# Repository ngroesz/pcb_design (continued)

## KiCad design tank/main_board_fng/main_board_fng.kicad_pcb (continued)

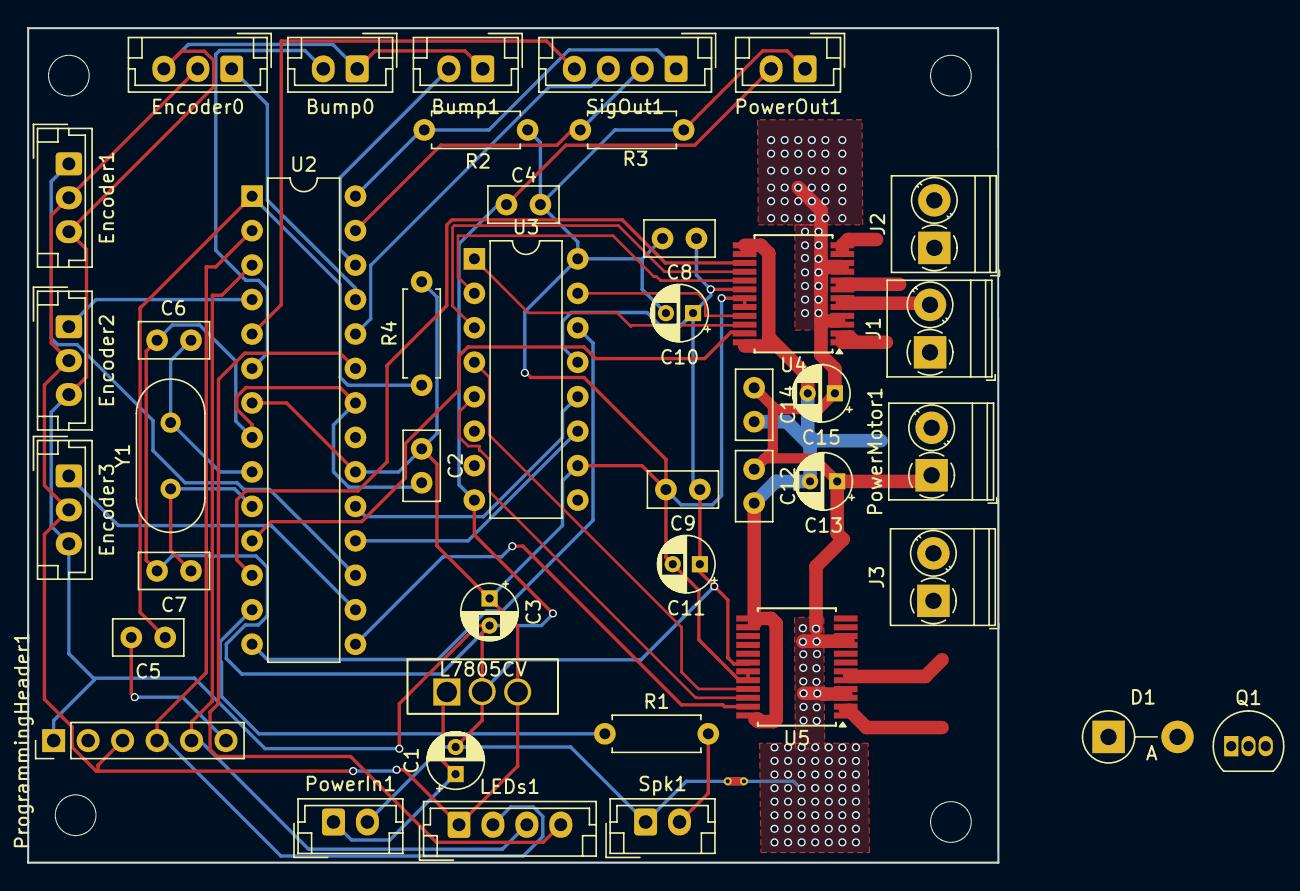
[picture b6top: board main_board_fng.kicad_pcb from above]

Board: 2 copper layers, 71.5 x 61.5 mm, 48 parts (0 on the bottom side), 44 nets.

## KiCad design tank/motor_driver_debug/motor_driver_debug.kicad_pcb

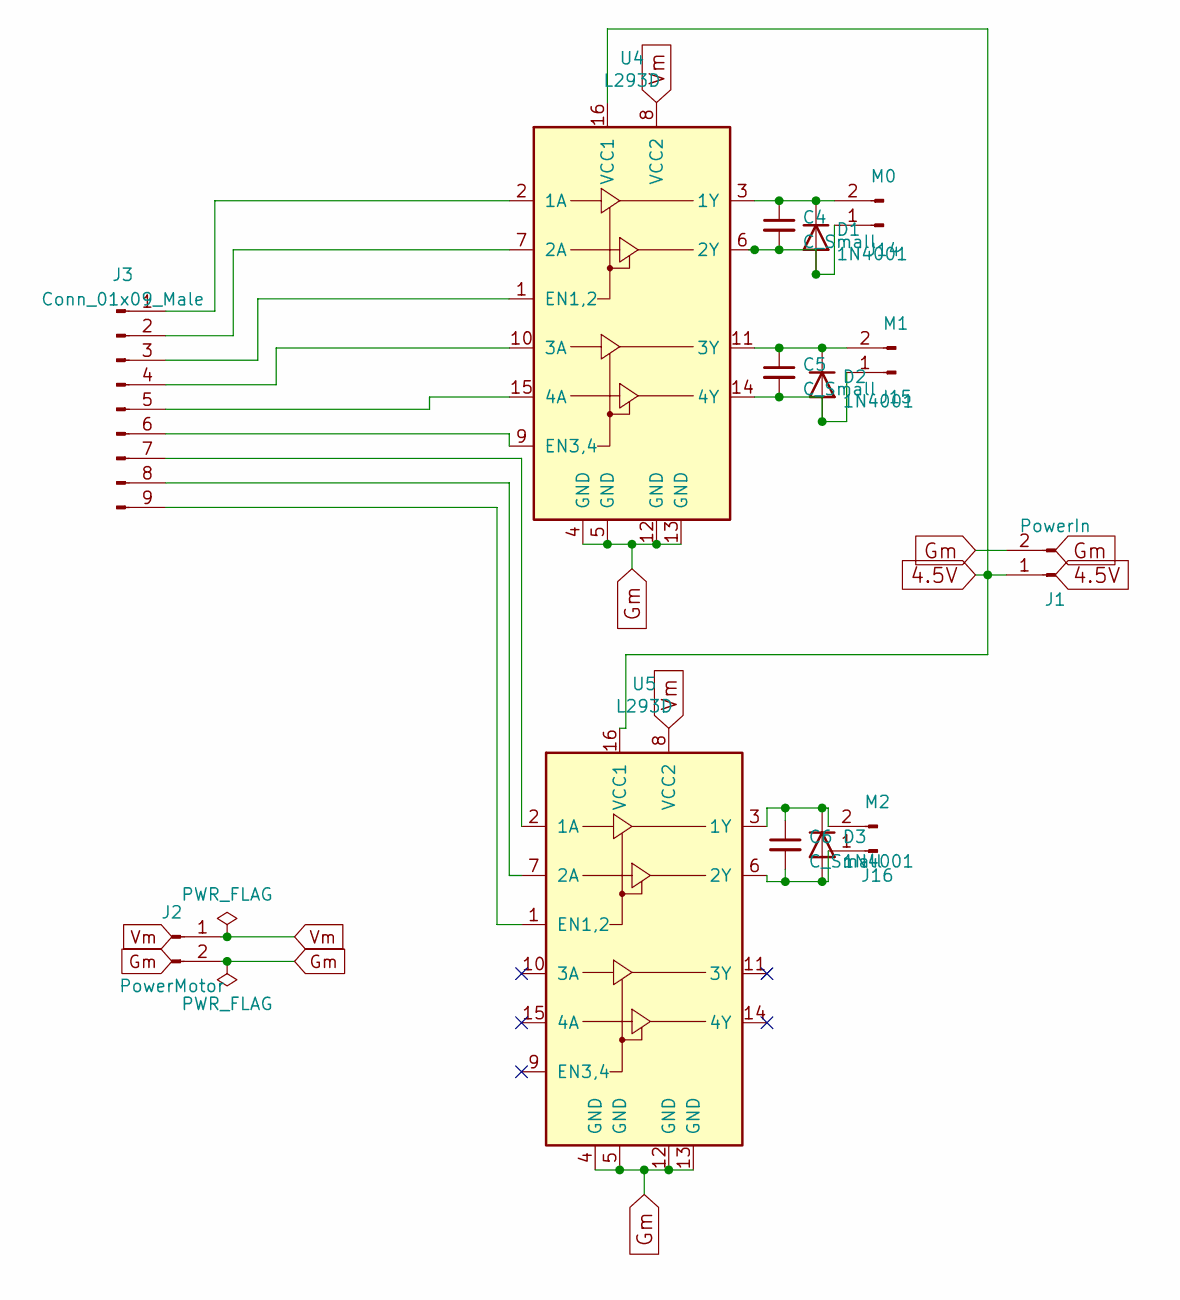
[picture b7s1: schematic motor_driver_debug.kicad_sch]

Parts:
C4, C5, C6: C_Small; C_Disc_D4.7mm_W2.5mm_P5.00mm
D1, D2, D3: 1N4001; D_DO-41_SOD81_P10.16mm_Horizontal
J1: PowerIn; JST_EH_B2B-EH-A_1x02_P2.50mm_Vertical
J2: PowerMotor; JST_EH_B2B-EH-A_1x02_P2.50mm_Vertical
J3: Conn_01x09_Male; JST_EH_B9B-EH-A_1x09_P2.50mm_Vertical
J14: M0; JST_EH_B2B-EH-A_1x02_P2.50mm_Vertical
J15: M1; JST_EH_B2B-EH-A_1x02_P2.50mm_Vertical
J16: M2; JST_EH_B2B-EH-A_1x02_P2.50mm_Vertical
U4, U5: L293D; DIP-16_W7.62mm

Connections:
4.5V: J1.1, U4.16 (VCC1), U5.16 (VCC1)
Gm: J1.2, J2.2, U4.4 (GND), U4.5 (GND), U4.12 (GND), U4.13 (GND), U5.4 (GND), U5.5 (GND), U5.12 (GND), U5.13 (GND)
unnamed: C4.1, D1.1 (K), J14.2, U4.3 (1Y)
unnamed: C4.2, D1.2 (A), J14.1, U4.6 (2Y)
unnamed: C5.1, D2.1 (K), J15.2, U4.11 (3Y)
unnamed: C5.2, D2.2 (A), J15.1, U4.14 (4Y)
unnamed: C6.1, D3.1 (K), J16.2, U5.3 (1Y)
unnamed: C6.2, D3.2 (A), J16.1, U5.6 (2Y)
unnamed: J3.1, U4.2 (1A)
unnamed: J3.2, U4.7 (2A)
unnamed: J3.3, U4.1 (EN1,2)
unnamed: J3.4, U4.10 (3A)
unnamed: J3.5, U4.15 (4A)
unnamed: J3.6, U4.9 (EN3,4)
unnamed: J3.7, U5.2 (1A)
unnamed: J3.8, U5.7 (2A)
unnamed: J3.9, U5.1 (EN1,2)
Vm: J2.1, U4.8 (VCC2), U5.8 (VCC2)

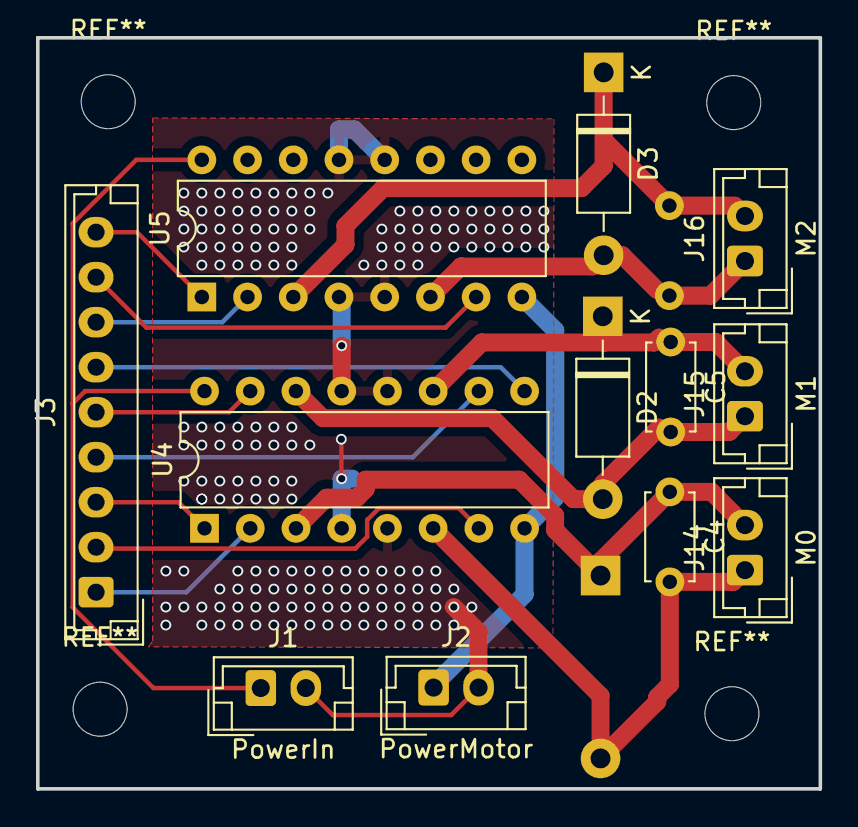
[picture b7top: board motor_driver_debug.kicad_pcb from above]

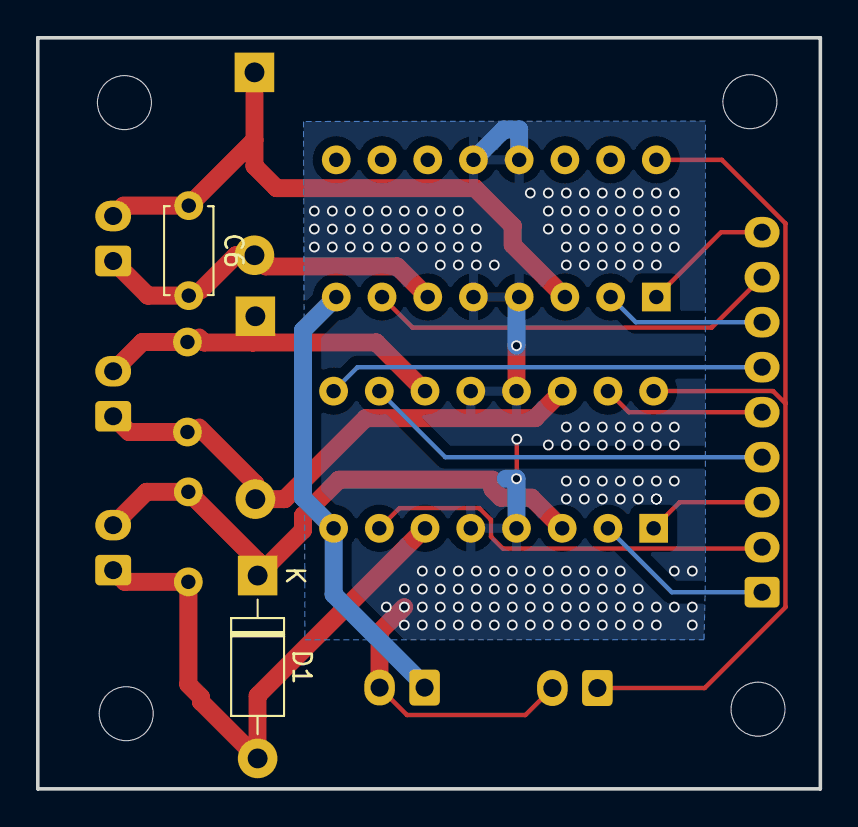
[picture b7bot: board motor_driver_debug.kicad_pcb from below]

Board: 2 copper layers, 43.5 x 41.7 mm, 14 parts (2 on the bottom side), 18 nets.

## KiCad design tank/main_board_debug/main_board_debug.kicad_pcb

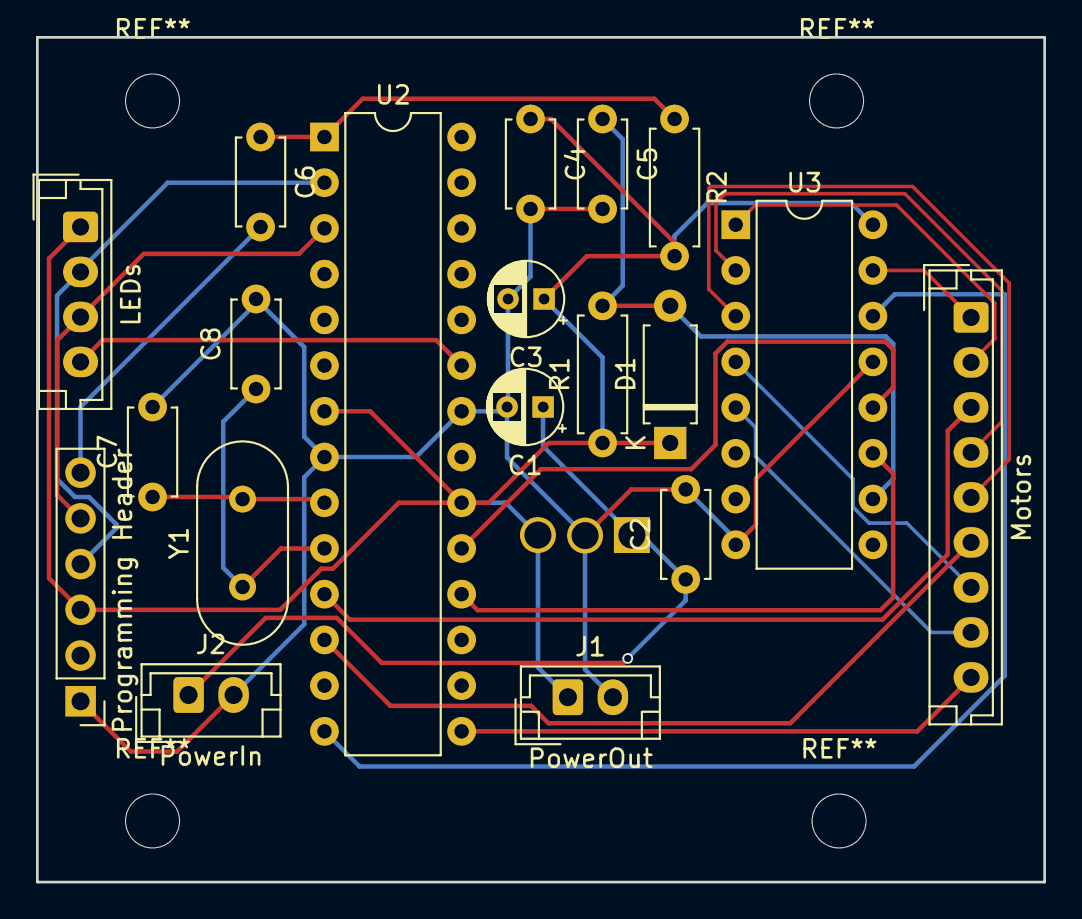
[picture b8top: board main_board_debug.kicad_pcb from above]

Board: 2 copper layers, 56.0 x 46.9 mm, 20 parts (0 on the bottom side), 23 nets.

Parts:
C1: CP1; CP_Radial_D4.0mm_P2.00mm
C2: C2; C_Disc_D4.7mm_W2.5mm_P5.00mm
C3: CP3; CP_Radial_D4.0mm_P2.00mm
C4: C4; C_Disc_D4.7mm_W2.5mm_P5.00mm
C5, C6: C_Small; C_Disc_D4.7mm_W2.5mm_P5.00mm
C7: C6; C_Disc_D4.7mm_W2.5mm_P5.00mm
C8: C7; C_Disc_D4.7mm_W2.5mm_P5.00mm
D1: D; D_A-405_P7.62mm_Horizontal
J1: PowerOut; JST_EH_B2B-EH-A_1x02_P2.50mm_Vertical
J2: PowerIn; JST_EH_B2B-EH-A_1x02_P2.50mm_Vertical
LEDs: LEDs; JST_EH_B4B-EH-A_1x04_P2.50mm_Vertical
Motors: Conn_01x09_Male; JST_EH_B9B-EH-A_1x09_P2.50mm_Vertical
Programming Header: Programming Header; PinHeader_1x06_P2.54mm_Vertical
R1: R; R_Axial_DIN0207_L6.3mm_D2.5mm_P7.62mm_Horizontal
R2: R10; R_Axial_DIN0207_L6.3mm_D2.5mm_P7.62mm_Horizontal
U1: L7805; L7805CV
U2: ATMEGA328P-PU; DIP-28_W7.62mm
U3: SN74HC595; DIP-16_W7.62mm
Y1: Crystal; Crystal_HC49-U_Vertical

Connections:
4.5V: C3.1, C4.1, D1.1 (K), J1.1, LEDs.1, Programming Header.3, R1.1, R2.2, U1.3 (OUT), U2.7 (VCC), U2.20 (AVCC), U3.16 (VCC)
9V: C1.1, C2.1, J2.1, U1.1 (IN)
GND: C1.2, C2.2, C3.2, C4.2, C5.2, C7.2, C8.2, J1.2, J2.2, Programming Header.1, U1.2 (GND), U2.8 (GND), U2.22 (GND), U3.8 (GND), U3.13 (G)
LED0: LEDs.2, Programming Header.4, U2.2 ((PCINT16/RXD)PD0)
LED1: LEDs.3, Programming Header.5, U2.3 ((PCINT17/TXD)PD1)
LED2: LEDs.4, U2.23 ((PCINT8/ADC0)PC0)
M0+: Motors.1, U3.15 (QA)
M0-: Motors.2, U3.1 (QB)
M0PWM: Motors.3, U2.11 ((PCINT21/OC0B/T1)PD5)
M1+: Motors.4, U3.2 (QC)
M1-: Motors.5, U3.3 (QD)
M1PWM: Motors.6, U2.12 ((PCINT22/OC0A/AIN0)PD6)
M2+: Motors.7, U3.4 (QE)
M2-: Motors.8, U3.5 (QF)
M2PWM: Motors.9, U2.15 ((PCINT1/OC1A)PB1)
unnamed: C5.1, D1.2 (A), R1.2, U3.10 (SRCLR)
unnamed: C6.1, R2.1, U2.1 ((PCINT14/~RESET)PC6)
unnamed: C6.2, Programming Header.6
unnamed: C7.1, U2.9 ((PCINT6/XTAL1/TOSC1)PB6), Y1.2
unnamed: C8.1, U2.10 ((PCINT7/XTAL2/TOSC2)PB7), Y1.1
SERIAL_CLOCK: U2.18 ((PCINT4/MISO)PB4), U3.11 (SRCLK)
SERIAL_DATA: U2.14 ((PCINT0/CLKO/ICP1)PB0), U3.14 (SER)
SERIAL_LATCH: U2.19 ((PCINT5/SCK)PB5), U3.12 (RCLK)

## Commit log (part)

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2017-10-29 main board v0.1
2017-10-29 Add modules
2017-10-30 notes
2017-11-11 turret board revisions
2017-11-11 Main Board v0.2
    Adjustments to main board:
    - resistors were inline when they shoulda been pull-ups
    - adjust crystal footprint
    - IR TX needs to be on pin 3
    - silkscreen should have component names
    - width of motor traces increased and added ground-fill
2017-11-12 interim
2017-11-13 Turret Board v0.4
2017-11-27 added todo file
2018-01-05 Main Board v0.3 - changed motor controllers to TB6612FNG - changed speaker transistor wiring - supports 4 LEDs, using switched ground
2018-01-17 Main Board v0.4
2018-02-03 shut er down
2020-04-15 migrate to KiCad 5.1.5
2020-04-15 remove backup files
2020-05-21 tank main board version 0.5: - separate power supplies - sonar connectors are now bump encoders - removed PWN line for turret motor
2020-05-22 Turret board version 0.5: - camera is integrated onto board
2020-05-31 LED strip
2020-05-31 remove unused trace
2020-06-06 Main Board version 0.6: - add ground planes on both layers - LED square is VCC - shorten board slightly - power out is regulated - vias. vias everywhere. - mounting holes embiggened
2020-06-10 Main Board Version 0.7
    Had to switch around pins. Need M0 and M1 on the same PWM timer.
    Need IR receiver pin to not interfere.
    No point in ground traces with a ground plane.
2020-06-16 LED strip version 0.2
    - fix orientation of LED footprints
    - fix unconnected traces (DOH.)
    - attempt to use local footprint library
2020-06-16 turret board interim
2021-09-25 LED version 0.3 - Cannot believe I screwed-up the footprints twice in a row. - Made a little wider for mounting-hole
2021-09-26 Turret Board Version 0.6: - change camera orientation to better fit in turret - updated footprints
2021-10-06 First version of Bump Sensor
2021-10-22 main board updates
2021-10-22 Bump Sensor Version 0.2 - make contact switch thru-holes bigger
2021-10-29 main board 0.8 WIP
2021-11-07 main board version 0.8
2021-11-30 and all that jazz
2021-12-01 l293d version
2021-12-23 L293 Breakout
2021-12-29 L298N breakout
2022-01-03 did i finally figure out the motor drivers?
2022-01-08 fix serial register
2022-01-09 version 0.10 (i hate kicad library management with every fibre of my being)
2022-02-02 I cannot believe that I screwed-up the Bump Sensor in such a dumb way and failed to run the design rule checker
2022-02-04 Major cleanup. I localized all the footprint and symbol libraries.
    I deleted most of the rescue stuff.
    I still need to finish-up changes to the turret board.
    Now this checkout should work "out of the box".
2022-02-08 fixes
2022-02-08 Version 0.11: - Better labelling - Put LED output on Rx and Tx pins. This way, we won't be attaching interrutps to Serial pins
2025-02-19 debug
2025-02-26 revisions
2025-02-26 turret board v0.8
2025-03-13 Main Board v0.12
2025-04-02 turret board v0.9
2025-04-05 modifying main board still need to finish PCB layout updates: - speaker gets resistor - net tie between logical ground and motor ground
    i would like to flip the motor ICs and add some more space
    around motor ICs and also a little more space around some of
    the JST connectors
2025-04-06 add some notes
2025-04-09 FNG WIP
2025-04-24 main board v0.14
2025-05-07 Main Board v0.15
    Changes:
    - back to L293 motor driver
    - add speaker resistor
    - 3.5mm pitch screw terminals for motors and motor power
    - move programming header
2025-05-07 Tank Trainer v0.1
2025-05-14 IR Camera v0.1
2025-05-16 IR Camera v0.2
2025-05-16 updates for a new version of main board, mostly just KiCAD fixes but this also includes a transistor for the speaker
2026-03-08 Turret Board v0.10: add connector for second I²C device
2026-03-08 update tank trainer to add programming header
2026-03-09 IR Camera v0.2: add programming header
2026-03-09 Main Board v0.16: Single power input
2026-03-14 tank trainer v0.2 (whoops ... forgot the button)
2026-04-11 minor changes for turret board v0.11
2026-04-15 Main Board version 0.17: - powerin is screw terminal footprint - removed PWM for turret and now both drive motors share PWM. this is because sharing the LEDs with Tx/Rx didn't work for Serial - chang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
2026-04-15 Main Board v0.17 Tank Trainer v0.3
2026-04-18 removed a bunch of old projects that were no longer used
2026-04-18 i think that all these files are no longer needed and for an earlier version of kicad
2026-05-12 checkin
2026-05-13 Main Board v0.18 Attempting to prevent uC reset due to motor noise and/or brownout - added TVS diode - added more capacitors
2026-06-27 Main board v0.19
2026-06-27 Main Board v0.19: - added capacitor to power input - removed TVS diode - reworked motor/power lines a bit - fixed some labels
